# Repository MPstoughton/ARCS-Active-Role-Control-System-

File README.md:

# ARCS-Active-Rocket-Control-System-

Precision in flight stability is a fundamental requirement for high-powered rocketry, directly influencing both mission safety and performance outcomes. Roll instability, in particular, can degrade aerodynamic efficiency, increase structural loading, and induce trajectory dispersions that compromise recovery reliability and payload success. Slender body rockets can be more inclined to experience unpredicted trajectories due to high roll rates. 

In the context of university and amateur rocketry programs, including the Intercollegiate Rocket Engineering Competition (IREC), NASA Student Launch Initiative (SLI), and the Friends of Amateur Rocketry OUT (FAR-OUT) competition, teams must address stability challenges while operating under strict limitations of weight, cost, and manufacturability. Competition-class rockets typically have masses between 20-40 kg, operate with peak dynamic pressures of 8–15 kPa, and are constrained to commercially available manufacturing processes. Within these regimes, any solution for roll stabilization must provide sufficient control authority while adding less than 1–2 percent to system mass and maintaining costs below approximately $500.

Conventional passive stabilization techniques, such as canted fins, generate roll torque through induced aerodynamic asymmetry but result in drag penalties that reduce apogee depending on Mach number and cant angle. Advanced active approaches, including thrust vector control, cold-gas thrusters, and reaction wheels, offer greater precision but impose significant penalties in mass, power, and cost. Consequently, there remains a clear technical gap for a lightweight, modular, and reliable roll control system tailored to the needs of competition-class rocketry.

The Active Rocket Control System (ARCS) project is conceived to address this gap by introducing an aerodynamic fin-based actuation mechanism capable of dynamically correcting roll during supersonic flight. The system integrates aerodynamic control surfaces with embedded actuation and onboard sensing, enabling closed-loop control of roll rates while minimizing drag penalties. The design emphasizes modularity, allowing integration into existing vehicles with minimal airframe modification, while maintaining manufacturability with student-accessible processes. Beyond roll control, the framework can be expanded to multi-axis stabilization, thereby serving as an enabling technology for advanced trajectory shaping, payload protection, and recovery optimization in future university-level aerospace programs.

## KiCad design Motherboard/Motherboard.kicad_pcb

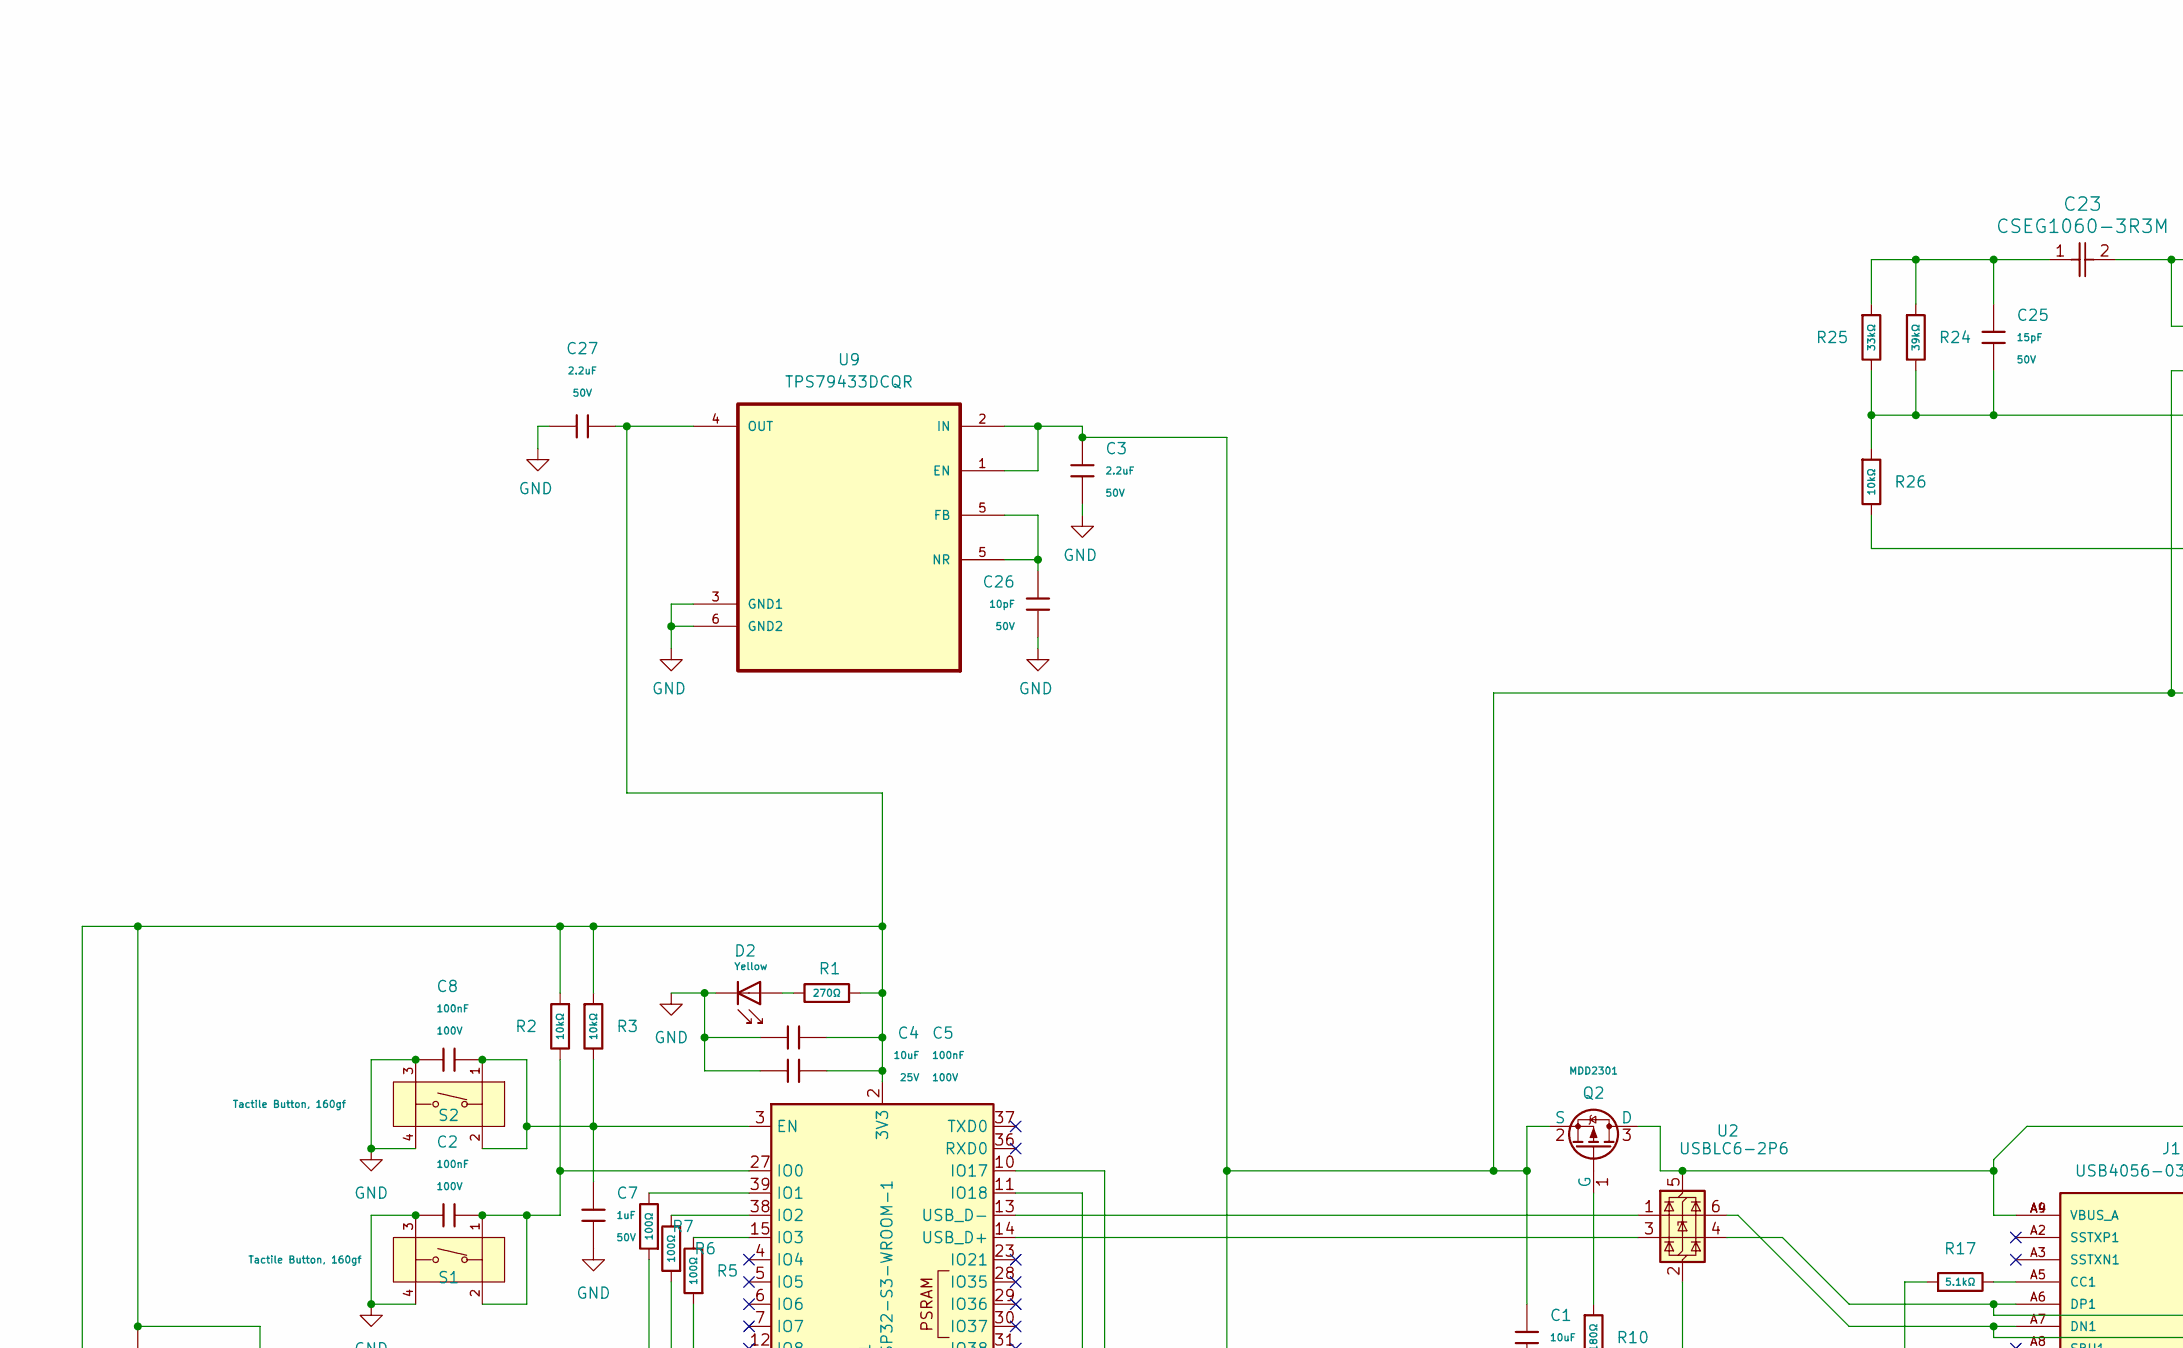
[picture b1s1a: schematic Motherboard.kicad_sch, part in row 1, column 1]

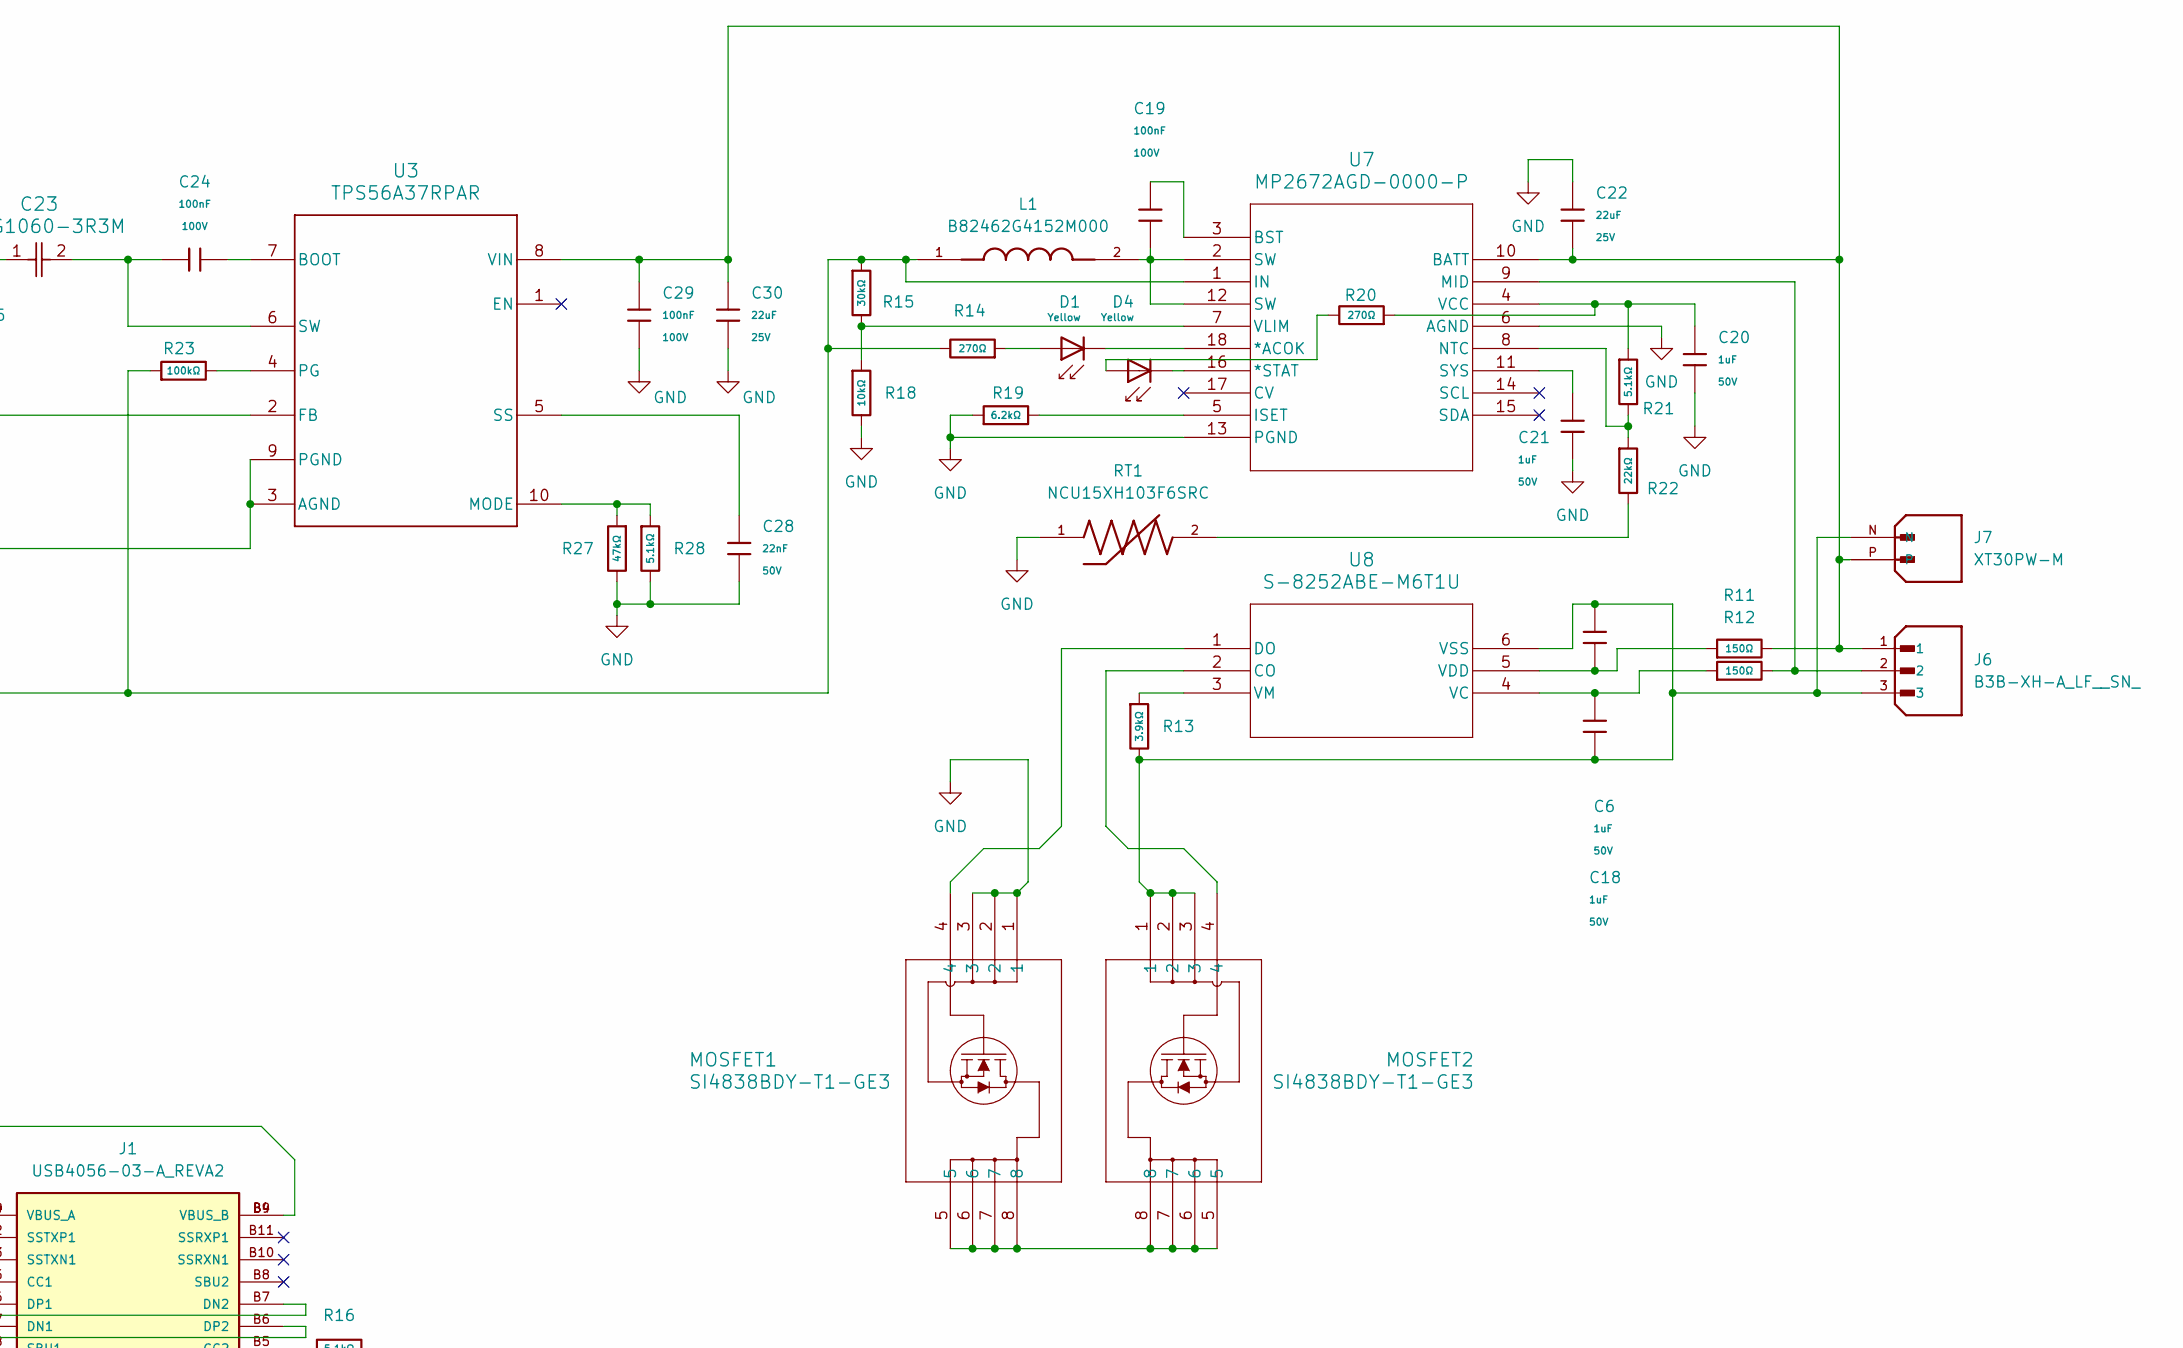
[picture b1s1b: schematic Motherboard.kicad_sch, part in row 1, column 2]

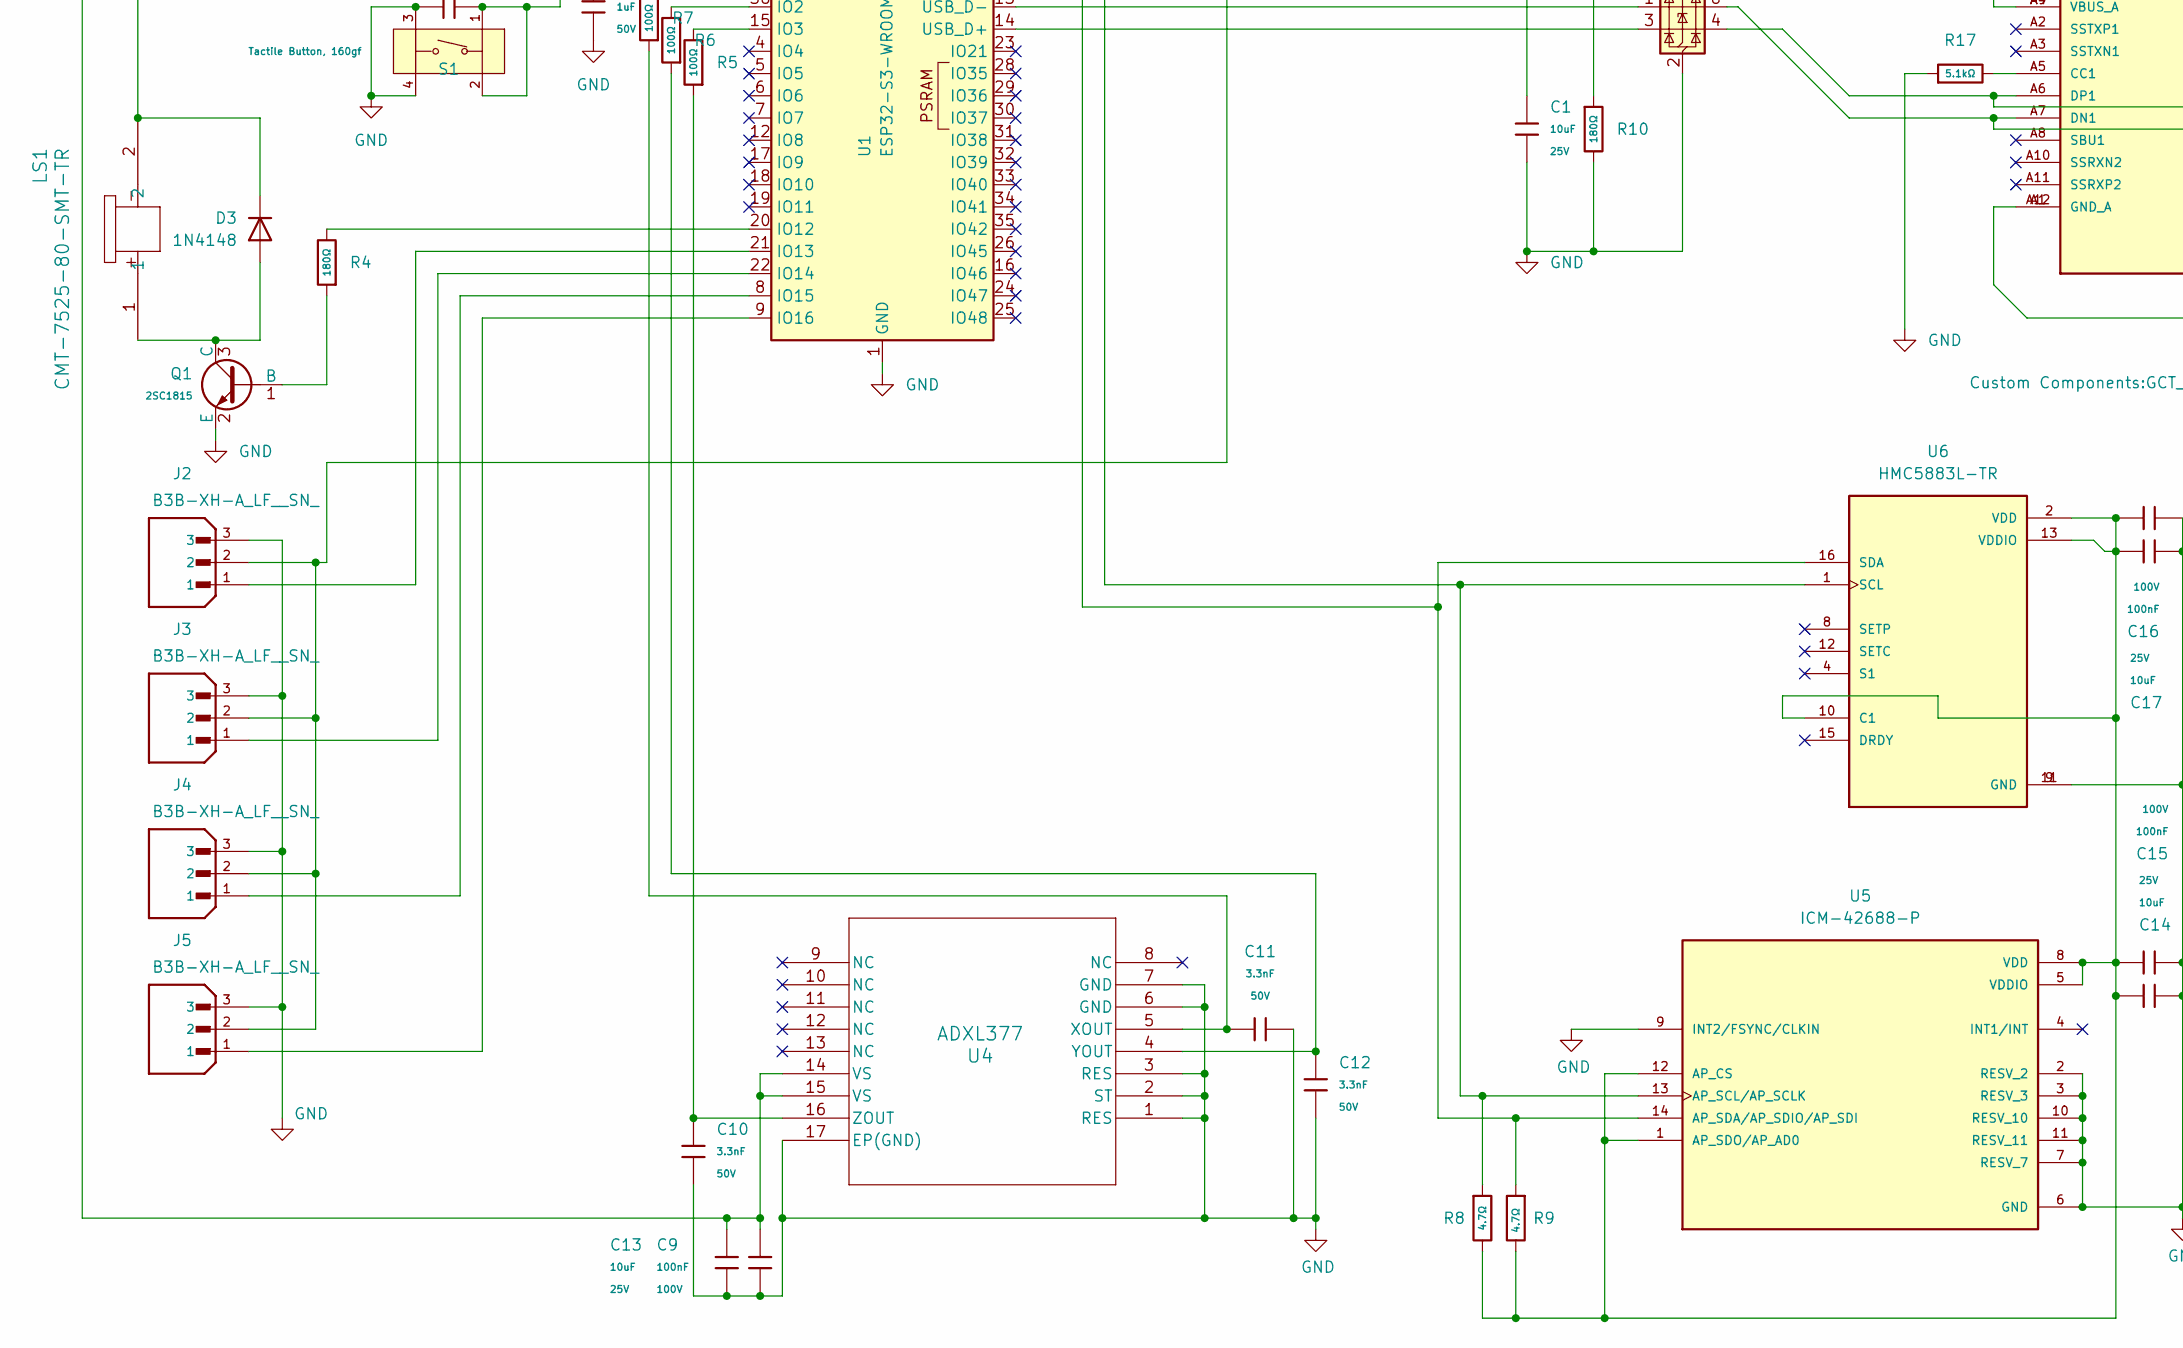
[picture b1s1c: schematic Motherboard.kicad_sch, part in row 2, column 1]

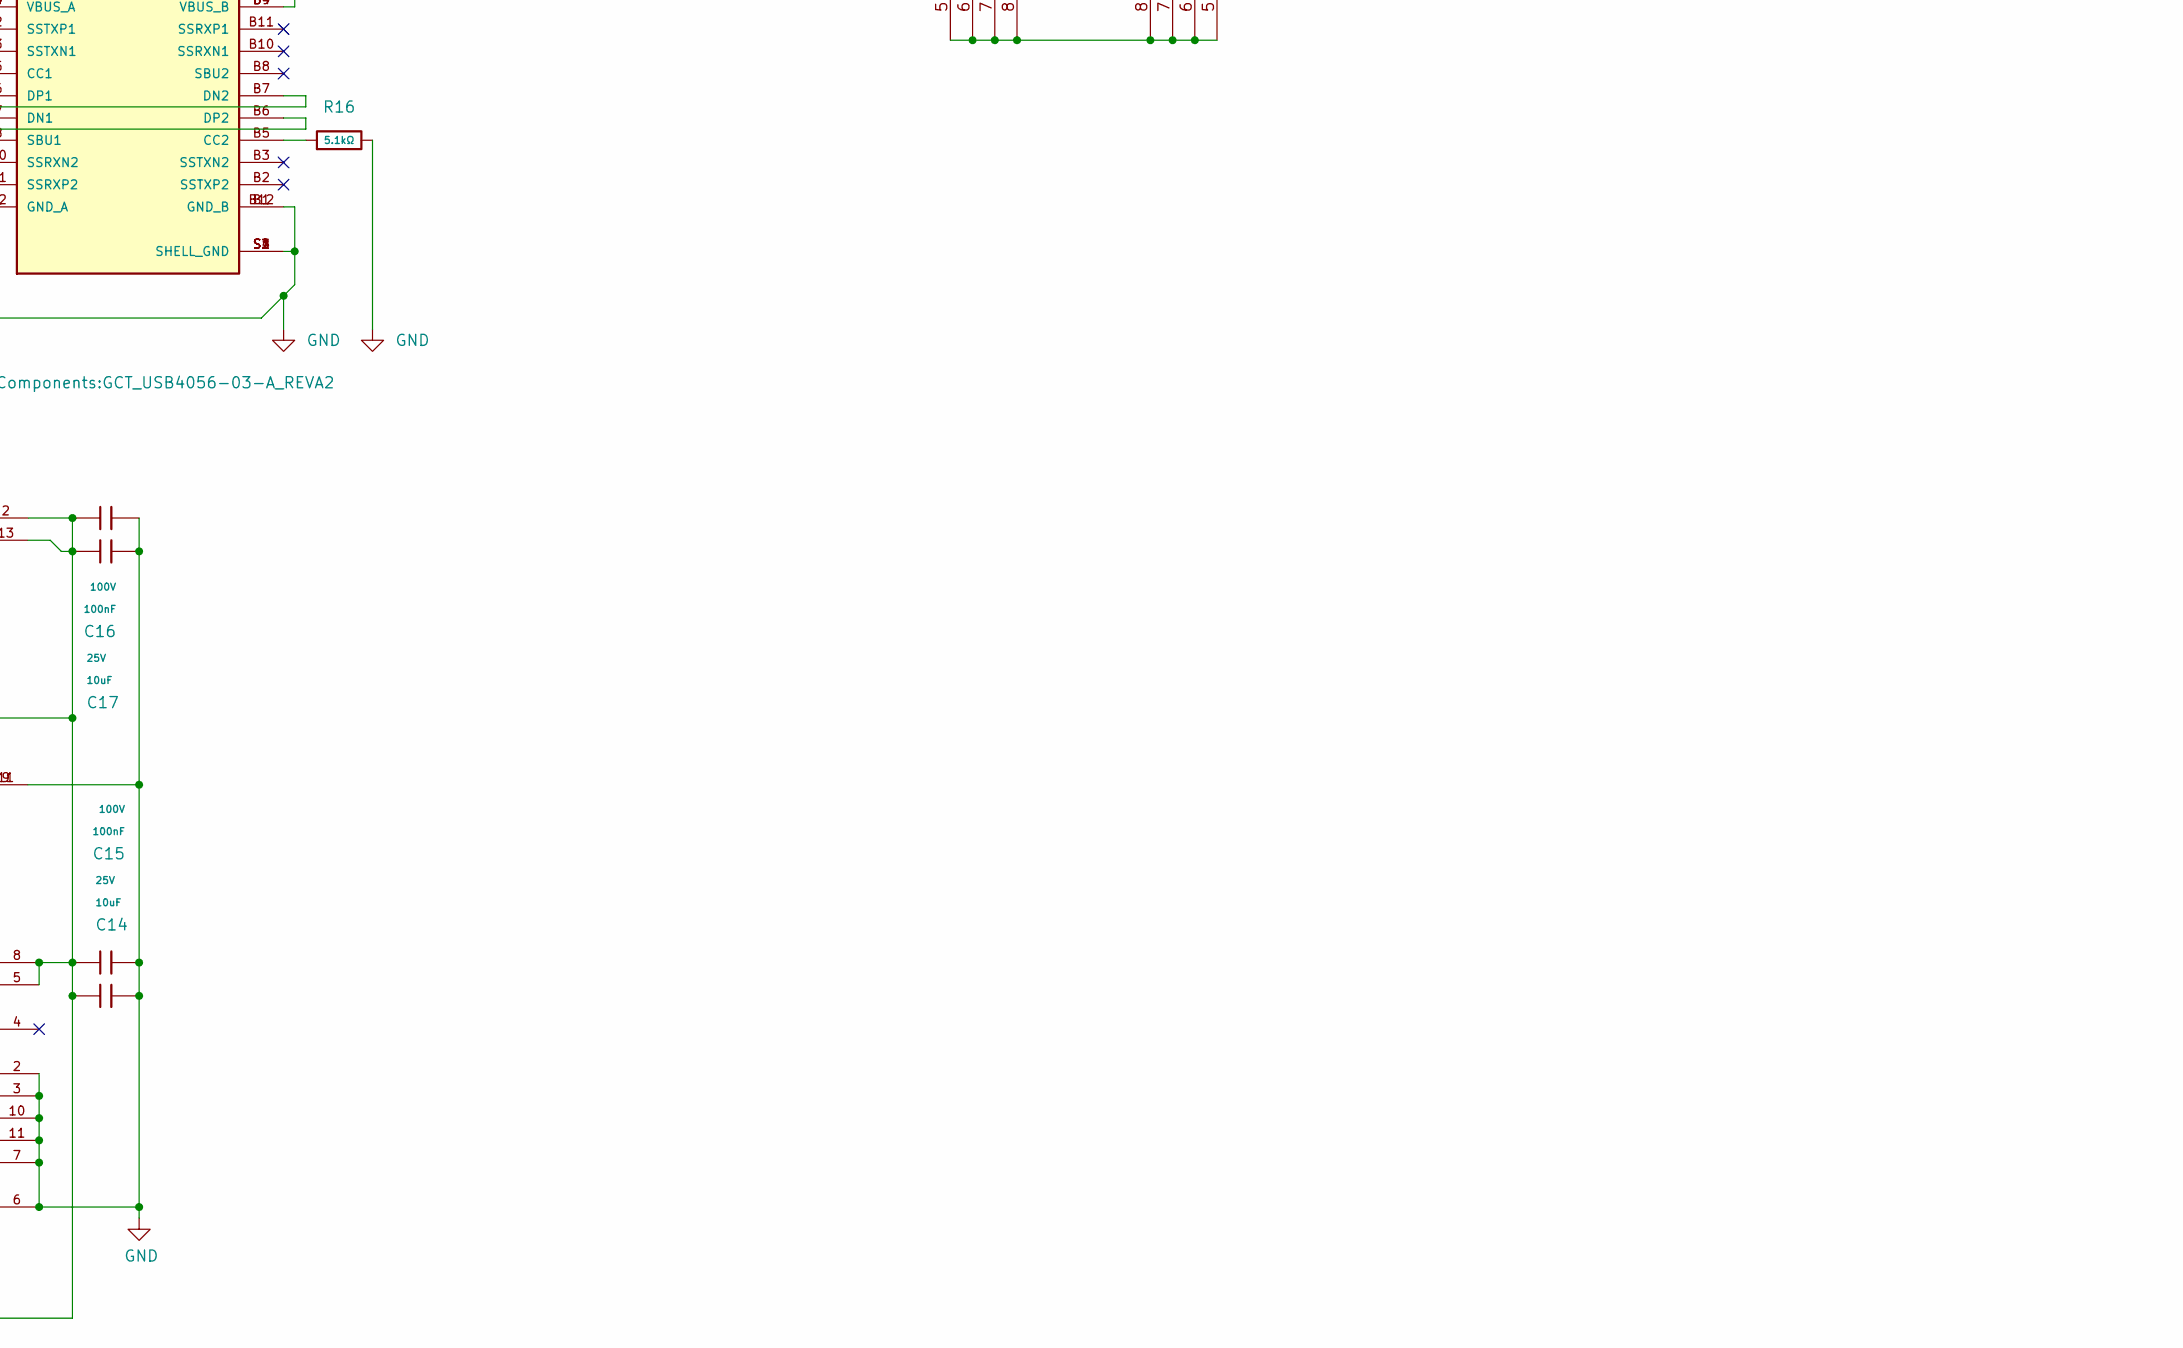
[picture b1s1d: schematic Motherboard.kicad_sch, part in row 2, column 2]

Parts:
C1, C4, C13, C14, C17: 10uF; C_0805; Voltage Rated 25V; Tolerance ±10%; Part CL21A106KAYNNNE; LCSC C15850
C2, C5, C8, C9, C15, C16, C19, C24, C29: 100nF; C_0805; Voltage Rated 100V; Tolerance ±10%; Part CL21B104KCFNNNE; LCSC C28233
C3, C27: 2.2uF; C_0805; Voltage Rated 50V; Tolerance ±10%; Part CL21A225KBQNNNE; LCSC C377773
C6, C7, C18, C20, C21: 1uF; C_0805; Voltage Rated 50V; Tolerance ±10%; Part CL21B105KBFNNNE; LCSC C28323
C10, C11, C12: 3.3nF; C_0603; Voltage Rated 50V; Tolerance ±10%; Part CL10B332KB8NNNC; LCSC C1613
C22, C30: 22uF; C_0805; Voltage Rated 25V; Tolerance ±20%; Part CL21A226MAQNNNE; LCSC C45783
C23: CSEG1060-3R3M; CAP_CSEG1060-3R3M_COD
C25: 15pF; C_0805; Voltage Rated 50V; Tolerance ±5%; Part CC0805JRNPO9BN150; LCSC C107110
C26: 10pF; C_0603; Voltage Rated 50V; Tolerance ±5%; Part CL10C100JB8NNNC; LCSC C1634
C28: 22nF; C_0805; Voltage Rated 50V; Tolerance ±10%; Part CL21B223KBANNNC; LCSC C1729
D1, D2, D4: Yellow; D_0805; Part KT-0805Y; LCSC C2296
D3: 1N4148; D_DO-35_SOD27_P7.62mm_Horizontal
J1: USB4056-03-A_REVA2; GCT_USB4056-03-A_REVA2; PARTREV A2; DigiKey_Part_Number 2073-USB4056-03-ACT-ND
J2, J3, J4, J5, J6: B3B-XH-A_LF__SN_; JST_B3B-XH-A_LF__SN_; PARTREV 7/4/21
J7: XT30PW-M; AMASS_XT30PW-M; PARTREV 1.2
L1: B82462G4152M000; IND_B82462G4152M000; PARTREV 2018-10
LS1: CMT-7525-80-SMT-TR; CMT-7525-80-SMT-TR_CUD
MOSFET1, MOSFET2: SI4838BDY-T1-GE3; SOIC8_NARROW_VIS
Q1: 2SC1815; Q_SOT-23; Part 2SC1815; LCSC C20069143
Q2: MDD2301; Q_SOT-23; Part MDD2301; LCSC C427391
R1, R14, R20: 270Ω; R_0805; Overload Voltage (Max) 150V; Tolerance ±1%; Part 0805W8F2700T5E; LCSC C17590
R2, R3, R26: 10kΩ; R_0805; Overload Voltage (Max) 150V; Tolerance ±1%; Part 0805W8F1002T5E; LCSC C17414
R4, R10: 180Ω; R_0805; Overload Voltage (Max) 150V; Tolerance ±1%; Part 0805W8F1800T5E; LCSC C25270
R5, R6, R7: 100Ω; R_0603; Overload Voltage (Max) 75V; Tolerance ±1%; Part 0603WAF1000T5E; LCSC C22775
R8, R9: 4.7Ω; R_0805; Overload Voltage (Max) 150V; Tolerance ±1%; Part 0805W8F470KT5E; LCSC C17675
R11, R12: 150Ω; R_0805; Overload Voltage (Max) 150V; Tolerance ±1%; Part 0805W8F1500T5E; LCSC C17471
R13: 3.9kΩ; R_0805; Overload Voltage (Max) 150V; Tolerance ±1%; Part 0805W8F3901T5E; LCSC C17614
R15: 30kΩ; R_0805; Overload Voltage (Max) 150V; Tolerance ±1%; Part 0805W8F3002T5E; LCSC C17621
R16, R17, R21, R28: 5.1kΩ; R_0805; Overload Voltage (Max) 150V; Tolerance ±1%; Part 0805W8F5101T5E; LCSC C27834
R18: 10kΩ; R_0603; Overload Voltage (Max) 75V; Tolerance ±1%; Part 0603WAF1002T5E; LCSC C25804
R19: 6.2kΩ; R_0805; Overload Voltage (Max) 150V; Tolerance ±1%; Part 0805W8F6201T5E; LCSC C17767
R22: 22kΩ; R_0805; Overload Voltage (Max) 150V; Tolerance ±1%; Part 0805W8F2202T5E; LCSC C17560
R23: 100kΩ; R_0805; Overload Voltage (Max) 150V; Tolerance ±1%; Part 0805W8F1003T5E; LCSC C149504
R24: 39kΩ; R_0805; Overload Voltage (Max) 150V; Tolerance ±1%; Part 0805W8F3902T5E; LCSC C25826
R25: 33kΩ; R_0805; Overload Voltage (Max) 150V; Tolerance ±1%; Part 0805W8F3302T5E; LCSC C17633
R27: 47kΩ; R_0805; Overload Voltage (Max) 150V; Tolerance ±1%; Part 0805W8F4702T5E; LCSC C17713
RT1: NCU15XH103F6SRC; THRMC1005X55N
S1, S2: Tactile Button, 160gf; SW-SMD_4P-L5.1-W5.1-P3.70-LS6.5-TL-2; Voltage Rating (Dc) 12V; Part TS-1187A-B-A-B; LCSC C318884
U1: ESP32-S3-WROOM-1
U2: USBLC6-2P6; SOT-666
U3: TPS56A37RPAR; RPA0010A-MFG
U4: ADXL377; CP_16_28_ADI
U5: ICM-42688-P; PQFN50P300X250X97-14N; PARTREV 1.2
U6: HMC5883L-TR; XDCR_HMC5883L-TR; PARTREV E
U7: MP2672AGD-0000-P; QFN-18_MP2672A_MNP
U8: S-8252ABE-M6T1U; SOT236-A-PKG_MP006-A-P-SD-2.1_ABL
U9: TPS79433DCQR; SOT127P706X180-6N; DigiKey_Part_Number 296-14437-1-ND

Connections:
GND: C1.2, C2.2, C3.1, C4.2, C5.2, C7.2, C8.2, C9.2, C10.1, C11.2, C12.1, C13.1, C14.1, C15.2, C16.2, C17.1, C20.2, C21.2, C22.1, C26.2, C27.1, C28.2, C29.2, C30.2, D2.1, J1.A1 (GND_A), J1.A12 (GND_A), J1.B1 (GND_B), J1.B12 (GND_B), J1.S1 (SHELL_GND), J1.S2 (SHELL_GND), J1.S3 (SHELL_GND), J1.S4 (SHELL_GND), J2.3, J3.3, J4.3, J5.3, MOSFET1.1, MOSFET1.2, MOSFET1.3, Q1.2 (E), R10.2, R16.2, R17.1, R18.2, R19.1, R27.2, R28.2, RT1.1, S1.3 (C), S1.4 (D), S2.3 (C), S2.4 (D), U1.1 (GND), U1.40 (GND), U1.41 (GND), U2.2 (GND), U4.1 (RES), U4.2 (ST), U4.3 (RES), U4.6 (GND), U4.7 (GND), U4.17 (EP(GND)), U5.2 (RESV_2), U5.3 (RESV_3), U5.6 (GND), U5.7 (RESV_7), U5.9 (INT2/FSYNC/CLKIN), U5.10 (RESV_10), U5.11 (RESV_11), U6.9 (GND), U6.11 (GND), U7.6 (AGND), U7.13 (PGND), U9.3 (GND1), U9.6 (GND2)
unnamed: C19.2, L1.2, U7.2 (SW), U7.12 (SW)
unnamed: C23.1, C25.1, R24.1, R25.1
unnamed: D1.2, R14.1
unnamed: D2.2, R1.2
unnamed: D3.2 (A), LS1.1, Q1.3 (C)
unnamed: C4.1, C5.1, C9.1, C13.2, C27.2, D3.1 (K), LS1.2, R1.1, R2.1, R3.1, U1.2 (3V3), U4.14 (VS), U4.15 (VS), U9.4 (OUT)
unnamed: D4.2, R20.2
unnamed: J1.A5 (CC1), R17.2
unnamed: J1.B5 (CC2), R16.1
unnamed: J1.A7 (DN1), J1.B6 (DP2), U2.6 (I/O1)
unnamed: J1.A6 (DP1), J1.B7 (DN2), U2.4 (I/O2)
unnamed: MOSFET1.5, MOSFET1.6, MOSFET1.7, MOSFET1.8, MOSFET2.5, MOSFET2.6, MOSFET2.7, MOSFET2.8
unnamed: Q1.1 (B), R4.1
unnamed: J1.A4 (VBUS_A), J1.A9 (VBUS_A), J1.B4 (VBUS_B), J1.B9 (VBUS_B), Q2.3 (D), U2.5 (VBUS)
unnamed: Q2.1 (G), R10.1
unnamed: C1.1, C3.2, J2.2, J3.2, J4.2, J5.2, L1.1, Q2.2 (S), R14.2, R15.1, R23.1, U7.1 (IN), U9.1 (EN), U9.2 (IN)
unnamed: R22.2, RT1.2
unnamed: C2.1, R2.2, S1.1 (A), S1.2 (B), U1.27 (IO0)
unnamed: C7.1, C8.1, R3.2, S2.1 (A), S2.2 (B), U1.3 (EN)
unnamed: R7.2, U1.39 (IO1)
unnamed: R6.2, U1.38 (IO2)
unnamed: R5.2, U1.15 (IO3)
unnamed: R4.2, U1.20 (IO12)
unnamed: J2.1, U1.21 (IO13)
unnamed: J3.1, U1.22 (IO14)
unnamed: J4.1, U1.8 (IO15)
unnamed: J5.1, U1.9 (IO16)
unnamed: R8.1, U1.10 (IO17), U5.13 (AP_SCL/AP_SCLK), U6.1 (SCL)
unnamed: R9.1, U1.11 (IO18), U5.14 (AP_SDA/AP_SDIO/AP_SDI), U6.16 (SDA)
unnamed: U1.14 (USB_D+), U2.3 (I/O2)
unnamed: U1.13 (USB_D-), U2.1 (I/O1)
unnamed: R26.2, U3.3 (AGND), U3.9 (PGND)
unnamed: C24.2, U3.7 (BOOT)
unnamed: C25.2, R24.2, R25.2, R26.1, U3.2 (FB)
unnamed: R27.1, R28.1, U3.10 (MODE)
unnamed: R23.2, U3.4 (PG)
unnamed: C28.1, U3.5 (SS)
unnamed: C23.2, C24.1, U3.6 (SW)
unnamed: C22.2, C29.1, C30.1, J6.1, J7.P, R11.2, U3.8 (VIN), U7.10 (BATT)
unnamed: C11.1, R7.1, U4.5 (XOUT)
unnamed: C12.2, R6.1, U4.4 (YOUT)
unnamed: C10.2, R5.1, U4.16 (ZOUT)
unnamed: C14.2, C15.1, C16.1, C17.2, R8.2, R9.2, U5.1 (AP_SDO/AP_AD0), U5.5 (VDDIO), U5.8 (VDD), U5.12 (AP_CS), U6.2 (VDD), U6.10 (C1), U6.13 (VDDIO)
unnamed: D1.1, U7.18 (*ACOK)
unnamed: D4.1, U7.16 (*STAT)
unnamed: C19.1, U7.3 (BST)
unnamed: R19.2, U7.5 (ISET)
unnamed: J6.2, R12.2, U7.9 (MID)
unnamed: R21.2, R22.1, U7.8 (NTC)
unnamed: C21.1, U7.11 (SYS)
unnamed: C20.1, R20.1, R21.1, U7.4 (VCC)
unnamed: R15.2, R18.1, U7.7 (VLIM)
unnamed: MOSFET2.4, U8.2 (CO)
unnamed: MOSFET1.4, U8.1 (DO)
unnamed: C18.1, R12.1, U8.4 (VC)
unnamed: C6.2, R11.1, U8.5 (VDD)
unnamed: R13.1, U8.3 (VM)
unnamed: C6.1, C18.2, J6.3, J7.N, MOSFET2.1, MOSFET2.2, MOSFET2.3, R13.2, U8.6 (VSS)
unnamed: C26.1, U9.5 (FB)

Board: 2 copper layers, 82 parts (0 on the bottom side), 59 nets, no tracks yet.

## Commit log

2025-10-07 adds a KiCAD project! :D
2025-10-08 does like everything
2025-10-14 adds bms system
2025-10-29 added bms system + buck converter
